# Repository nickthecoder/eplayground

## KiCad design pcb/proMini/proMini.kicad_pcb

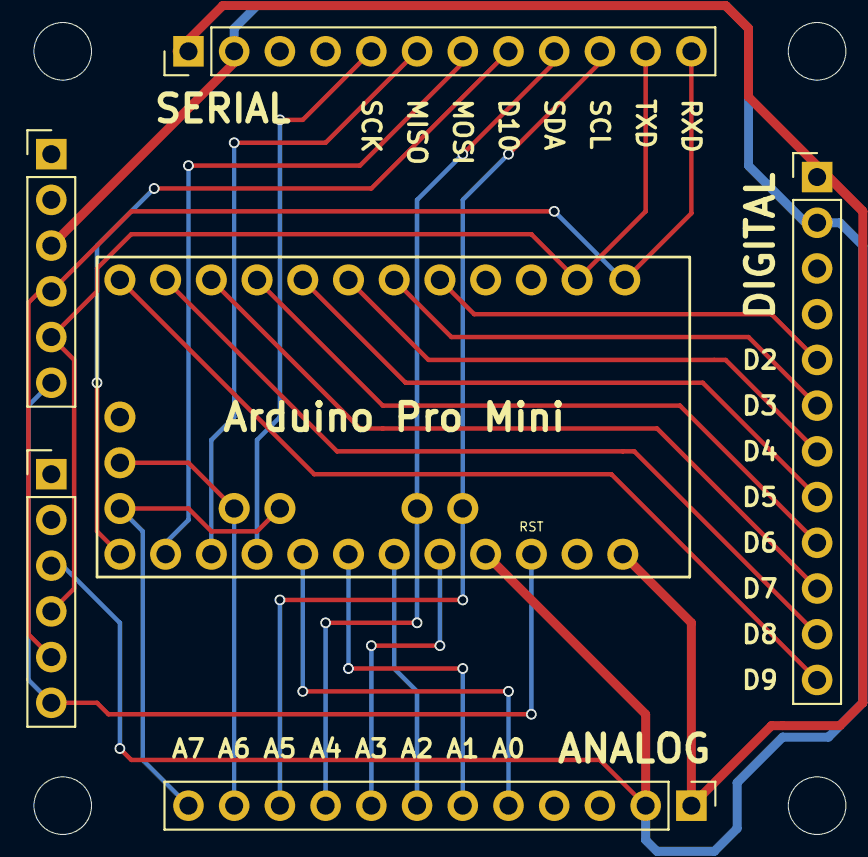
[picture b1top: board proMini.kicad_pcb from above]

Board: 2 copper layers, 8 parts (0 on the bottom side), 26 nets.

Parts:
FT1, FT2: FTDI; Pin_Header_Straight_1x06_Pitch2.54mm
O1: SerialOutput; Socket_Strip_Straight_1x12_Pitch2.54mm
O2, O3: Output; Socket_Strip_Straight_1x12_Pitch2.54mm
X: M3; MountingHole_3.2mm_M3
X#2: M3; MountingHole_3.2mm_M3
XA1: Arduino_Mini_01_Socket; Arduino_ProMini_NoICSP

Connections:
/A0: O3.5, XA1.A0
/A1: O3.6, XA1.A1
/A2: O3.7, XA1.A2
/A3: O3.8, XA1.A3
/A4: O1.9, O3.9, XA1.A4
/A5: O1.10, O3.10, XA1.A5
/A6: O3.11, XA1.A6
/A7: O3.12, XA1.A7
/D0: FT1.5, FT2.4, O1.12, XA1.D0
/D1: FT1.4, FT2.5, O1.11, XA1.D1
/D2: O2.5, XA1.D2
/D3: O2.6, XA1.D3
/D4: O2.7, XA1.D4
/D5: O2.8, XA1.D5
/D6: O2.9, XA1.D6
/D7: O2.10, XA1.D7
/D8: O2.11, XA1.D8
/D9: O2.12, XA1.D9
/D10: O1.8, XA1.D10
/D11: O1.7, XA1.D11
/D12: O1.6, XA1.D12
/D13: O1.5, XA1.D13
/GND: FT1.1, FT1.2, FT2.1, FT2.2, O1.3, O2.3, O3.3, XA1.GND2, XA1.GND4
/RESET: FT1.6, FT2.6, XA1.RST2
/VCC: FT1.3, FT2.3, O1.2, O2.2, O3.2, XA1.5V1
/VIN: O1.1, O2.1, O3.1, XA1.VIN

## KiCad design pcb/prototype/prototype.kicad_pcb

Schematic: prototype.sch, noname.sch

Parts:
H1: Headers8L; Pin_Header_Straight_1x08_Pitch2.54mm
H4: Headers8; Pin_Header_Straight_1x08_Pitch2.54mm
I1, I2: Input; Pin_Header_Straight_1x12_Pitch2.54mm
J1, J2, J3, J4, J5, J6, J7, J8: GS2
J9, J10, J11: Conn_01x14; Pin_Header_Straight_1x14_Pitch2.54mm
J12, J13: Conn_01x08; Pin_Header_Straight_1x08_Pitch2.54mm
O1, O2: Output; Socket_Strip_Straight_1x12_Pitch2.54mm

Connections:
/L0: H1.1 (H1), I1.5 (L0), J1.2 (G2)
/L1: H1.2 (H2), I1.6 (L1), J2.2 (G2)
/L2: H1.3 (H3), I1.7 (L2), J3.2 (G2)
/L3: H1.4 (H4), I1.8 (L3), J4.2 (G2)
/L4: H1.5 (H5), I1.9 (L4), J5.2 (G2)
/L5: H1.6 (H6), I1.10 (L5), J6.2 (G2)
/L6: H1.7 (H7), I1.11 (L6), J7.2 (G2)
/L7: H1.8 (H8), I1.12 (L7), J8.2 (G2)
/VCC: I1.2 (VCC), I2.2 (VCC), J10.1, J10.2, J10.3, J10.4, J10.5, J10.6, J10.7, J10.8, J10.9, J10.10, J10.11, J10.12, J10.13, J10.14, O1.2 (VCC), O2.2 (VCC)
/VIN: I1.1 (VIN), I2.1 (VIN), J11.1, J11.2, J11.3, J11.4, J11.5, J11.6, J11.7, J11.8, J11.9, J11.10, J11.11, J11.12, J11.13, J11.14, O1.1 (VIN), O2.1 (VIN)
Earth: I1.3 (GND), I2.3 (GND), J9.1, J9.2, J9.3, J9.4, J9.5, J9.6, J9.7, J9.8, J9.9, J9.10, J9.11, J9.12, J9.13, J9.14, O1.3 (GND), O2.3 (GND)
unnamed: H4.1 (H1), J1.1 (G1), O2.5 (L0)
unnamed: H4.2 (H2), J2.1 (G1), O2.6 (L1)
unnamed: H4.3 (H3), J3.1 (G1), O2.7 (L2)
unnamed: H4.4 (H4), J4.1 (G1), O2.8 (L3)
unnamed: H4.5 (H5), J5.1 (G1), O2.9 (L4)
unnamed: H4.6 (H6), J6.1 (G1), O2.10 (L5)
unnamed: H4.7 (H7), J7.1 (G1), O2.11 (L6)
unnamed: H4.8 (H8), J8.1 (G1), O2.12 (L7)
unnamed: I2.5 (L0), J13.1
unnamed: I2.6 (L1), J13.2
unnamed: I2.7 (L2), J13.3
unnamed: I2.8 (L3), J13.4
unnamed: I2.9 (L4), J13.5
unnamed: I2.10 (L5), J13.6
unnamed: I2.11 (L6), J13.7
unnamed: I2.12 (L7), J13.8
unnamed: J12.1, O1.12 (L7)
unnamed: J12.2, O1.11 (L6)
unnamed: J12.3, O1.10 (L5)
unnamed: J12.4, O1.9 (L4)
unnamed: J12.5, O1.8 (L3)
unnamed: J12.6, O1.7 (L2)
unnamed: J12.7, O1.6 (L1)
unnamed: J12.8, O1.5 (L0)

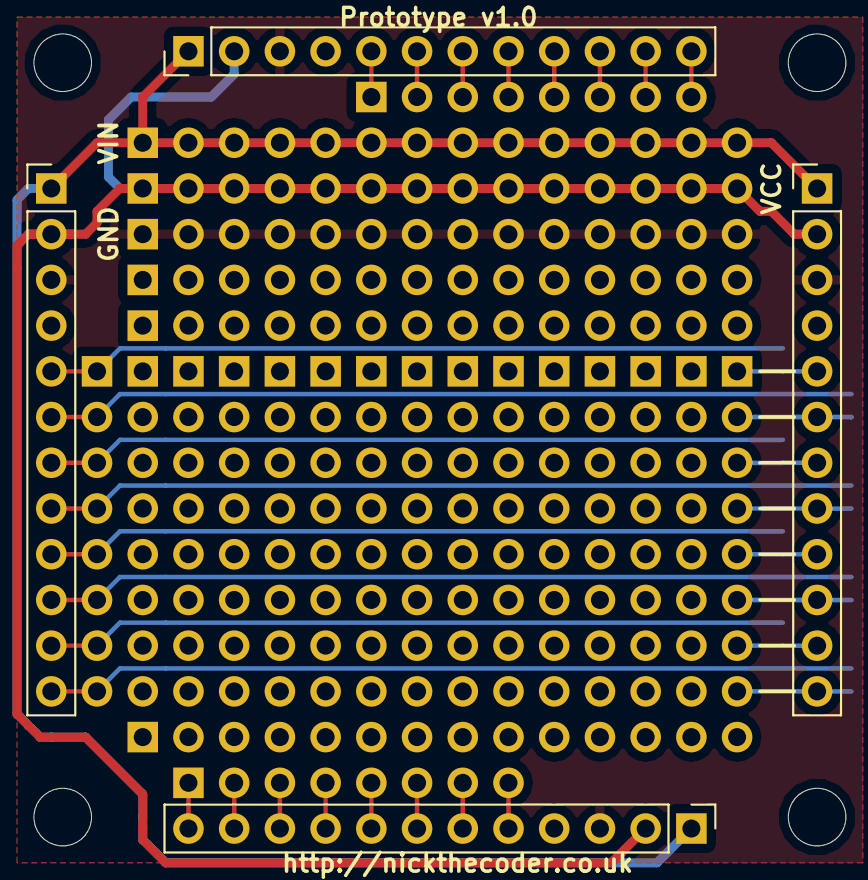
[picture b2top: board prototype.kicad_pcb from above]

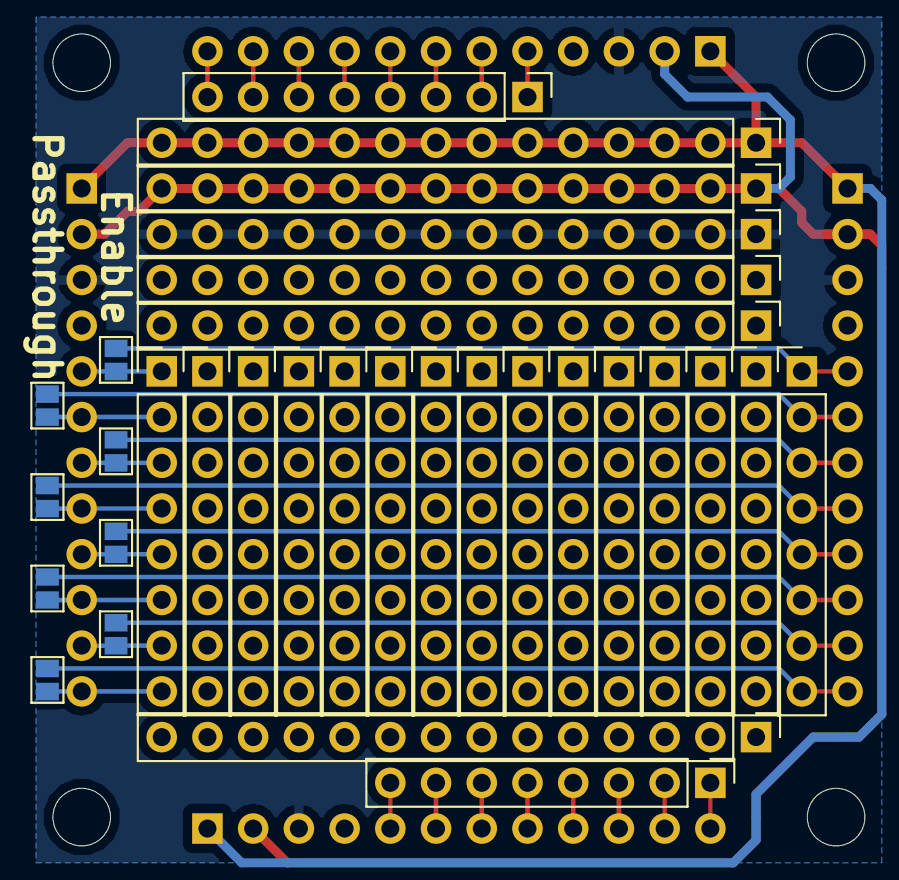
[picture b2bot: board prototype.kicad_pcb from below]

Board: 2 copper layers, 21 parts (15 on the bottom side), 35 nets.

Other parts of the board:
M3, M3#2: MountingHole_3.2mm_M3

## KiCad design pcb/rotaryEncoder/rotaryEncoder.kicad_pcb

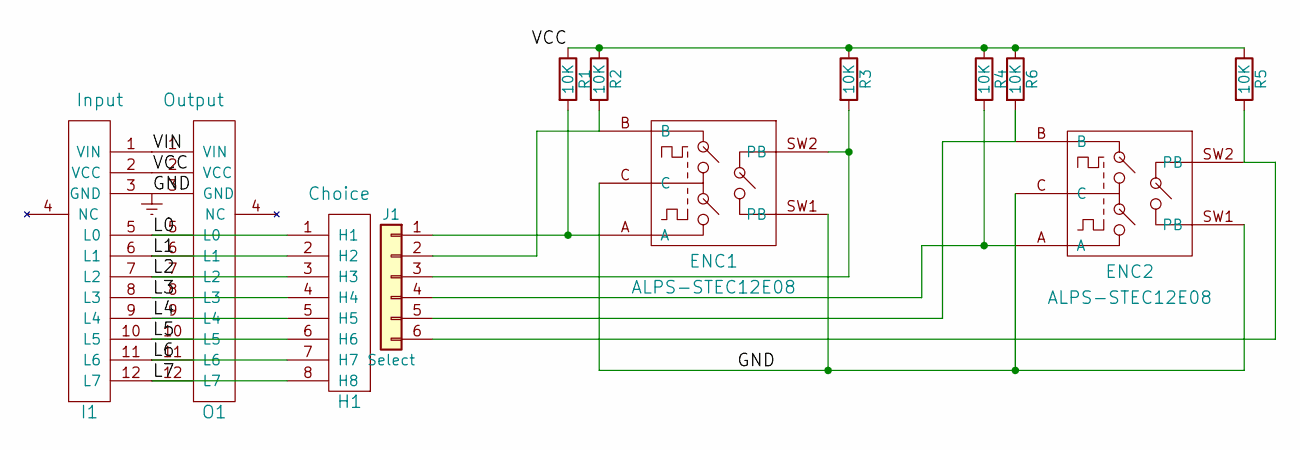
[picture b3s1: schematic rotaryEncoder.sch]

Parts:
ENC1, ENC2: ALPS-STEC12E08; ALPS_STEC12E08
H1: Choice; Pin_Header_Straight_1x08_Pitch2.54mm
I1: Input; Pin_Header_Straight_1x12_Pitch2.54mm
J1: Select; Pin_Header_Straight_1x06_Pitch2.54mm
O1: Output; Socket_Strip_Straight_1x12_Pitch2.54mm
R1, R2, R3, R4, R5, R6: 10K; R_Axial_DIN0204_L3.6mm_D1.6mm_P7.62mm_Horizontal

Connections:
/L0: H1.1 (H1), I1.5 (L0), O1.5 (L0)
/L1: H1.2 (H2), I1.6 (L1), O1.6 (L1)
/L2: H1.3 (H3), I1.7 (L2), O1.7 (L2)
/L3: H1.4 (H4), I1.8 (L3), O1.8 (L3)
/L4: H1.5 (H5), I1.9 (L4), O1.9 (L4)
/L5: H1.6 (H6), I1.10 (L5), O1.10 (L5)
/L6: H1.7 (H7), I1.11 (L6), O1.11 (L6)
/L7: H1.8 (H8), I1.12 (L7), O1.12 (L7)
/VCC: I1.2 (VCC), O1.2 (VCC), R1.1, R2.1, R3.1, R4.1, R5.1, R6.1
/VIN: I1.1 (VIN), O1.1 (VIN)
Earth: ENC1.C, ENC1.SW1 (PB), ENC2.C, ENC2.SW1 (PB), I1.3 (GND), O1.3 (GND)
unnamed: ENC1.A, J1.1, R1.2
unnamed: ENC1.B, J1.2, R2.2
unnamed: ENC1.SW2 (PB), J1.3, R3.2
unnamed: ENC2.A, J1.4, R4.2
unnamed: ENC2.B, J1.5, R6.2
unnamed: ENC2.SW2 (PB), J1.6, R5.2

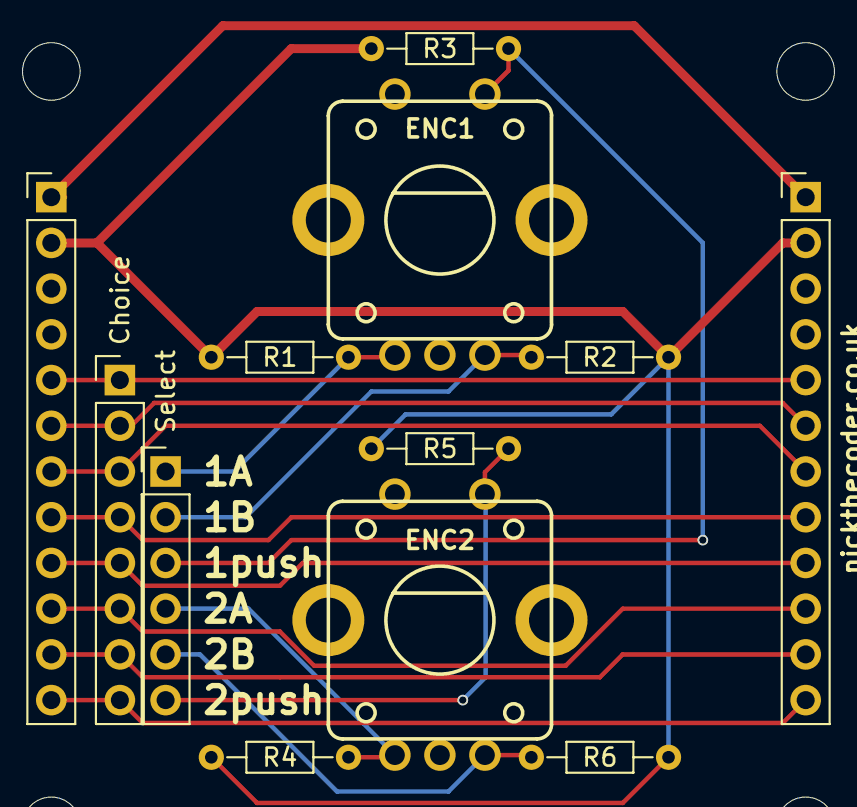
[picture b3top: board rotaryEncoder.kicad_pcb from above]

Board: 2 copper layers, 14 parts (0 on the bottom side), 17 nets.

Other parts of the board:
M3, M3#2: MountingHole_3.2mm_M3

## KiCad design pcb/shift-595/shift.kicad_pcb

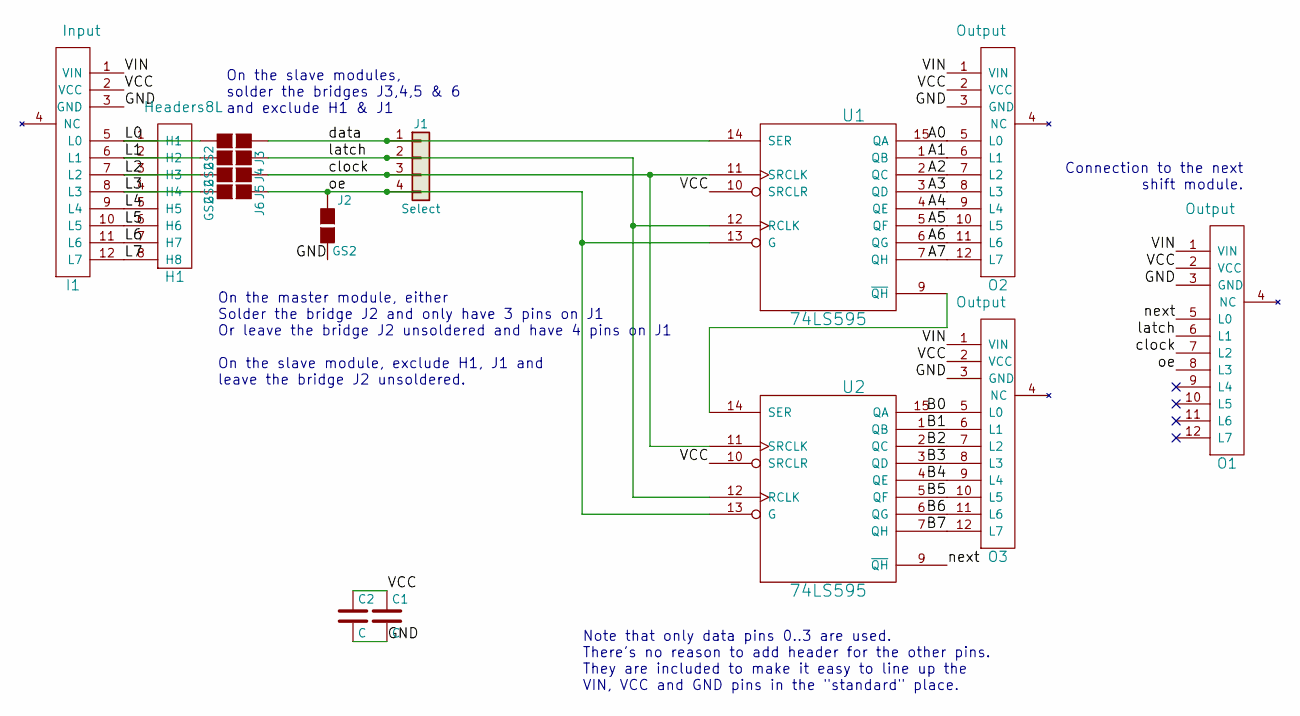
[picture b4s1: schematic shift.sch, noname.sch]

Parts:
C1, C2: C; C_Disc_D3.0mm_W2.0mm_P2.50mm
H1: Headers8L; Pin_Header_Straight_1x08_Pitch2.54mm
I1: Input; Pin_Header_Straight_1x12_Pitch2.54mm
J1: Select; Pin_Header_Straight_1x04_Pitch2.54mm
J2, J3, J4, J5, J6: GS2
O1, O2, O3: Output; Socket_Strip_Straight_1x12_Pitch2.54mm
U1, U2: 74LS595; DIP-16_W7.62mm

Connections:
/A0: O2.5 (L0), U1.15 (QA)
/A1: O2.6 (L1), U1.1 (QB)
/A2: O2.7 (L2), U1.2 (QC)
/A3: O2.8 (L3), U1.3 (QD)
/A4: O2.9 (L4), U1.4 (QE)
/A5: O2.10 (L5), U1.5 (QF)
/A6: O2.11 (L6), U1.6 (QG)
/A7: O2.12 (L7), U1.7 (QH)
/B0: O3.5 (L0), U2.15 (QA)
/B1: O3.6 (L1), U2.1 (QB)
/B2: O3.7 (L2), U2.2 (QC)
/B3: O3.8 (L3), U2.3 (QD)
/B4: O3.9 (L4), U2.4 (QE)
/B5: O3.10 (L5), U2.5 (QF)
/B6: O3.11 (L6), U2.6 (QG)
/B7: O3.12 (L7), U2.7 (QH)
/L0: H1.1 (H1), I1.5 (L0), J3.2 (G2)
/L1: H1.2 (H2), I1.6 (L1), J4.2 (G2)
/L2: H1.3 (H3), I1.7 (L2), J5.2 (G2)
/L3: H1.4 (H4), I1.8 (L3), J6.2 (G2)
/L4: H1.5 (H5), I1.9 (L4)
/L5: H1.6 (H6), I1.10 (L5)
/L6: H1.7 (H7), I1.11 (L6)
/L7: H1.8 (H8), I1.12 (L7)
/VIN: I1.1 (VIN), O1.1 (VIN), O2.1 (VIN), O3.1 (VIN)
/clock: J1.3, J5.1 (G1), O1.7 (L2), U1.11 (SRCLK), U2.11 (SRCLK)
/data: J1.1, J3.1 (G1), U1.14 (SER)
/latch: J1.2, J4.1 (G1), O1.6 (L1), U1.12 (RCLK), U2.12 (RCLK)
/next: O1.5 (L0), U2.9 (~QH)
/oe: J1.4, J2.1 (G1), J6.1 (G1), O1.8 (L3), U1.13 (G), U2.13 (G)
GND: C1.2, C2.2, I1.3 (GND), J2.2 (G2), O1.3 (GND), O2.3 (GND), O3.3 (GND), U1.8 (GND), U2.8 (GND)
unnamed: U1.9 (~QH), U2.14 (SER)
VCC: C1.1, C2.1, I1.2 (VCC), O1.2 (VCC), O2.2 (VCC), O3.2 (VCC), U1.10 (SRCLR), U1.16 (VCC), U2.10 (SRCLR), U2.16 (VCC)

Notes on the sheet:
Connection to the next shift module.
Note that only data pins 0..3 are used. There's no reason to add header for the other pins. They are included to make it easy to line up the VIN, VCC and GND pins in the "standard" place.
On the master module, either Solder the bridge J2 and only have 3 pins on J1 Or leave the bridge J2 unsoldered and have 4 pins on J1 On the slave module, exclude H1, J1 and leave the bridge J2 unsoldered.
On the slave modules, solder the bridges J3,4,5 & 6 and exclude H1 & J1

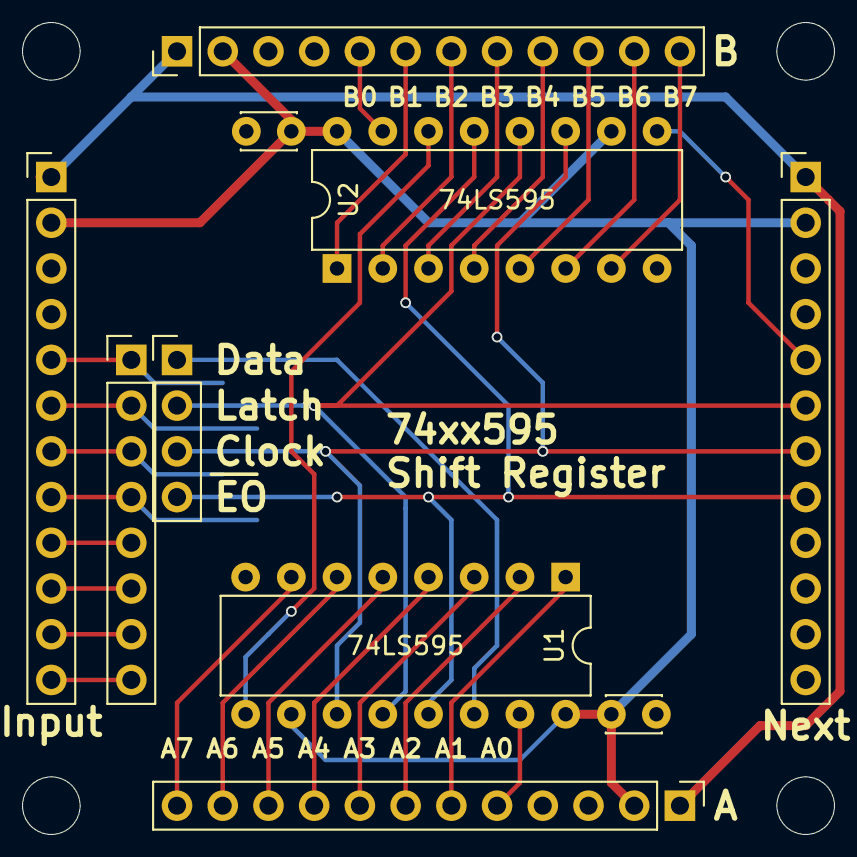
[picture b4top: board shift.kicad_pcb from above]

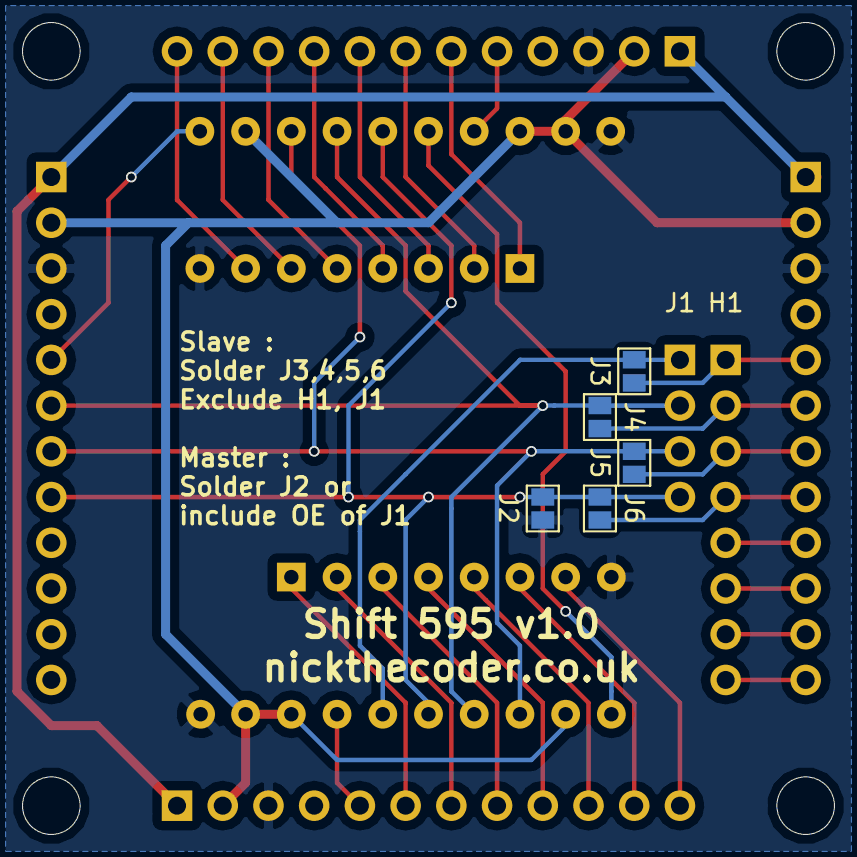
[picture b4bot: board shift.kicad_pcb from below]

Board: 2 copper layers, 17 parts (5 on the bottom side), 33 nets.

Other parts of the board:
M3, M3#2: MountingHole_3.2mm_M3

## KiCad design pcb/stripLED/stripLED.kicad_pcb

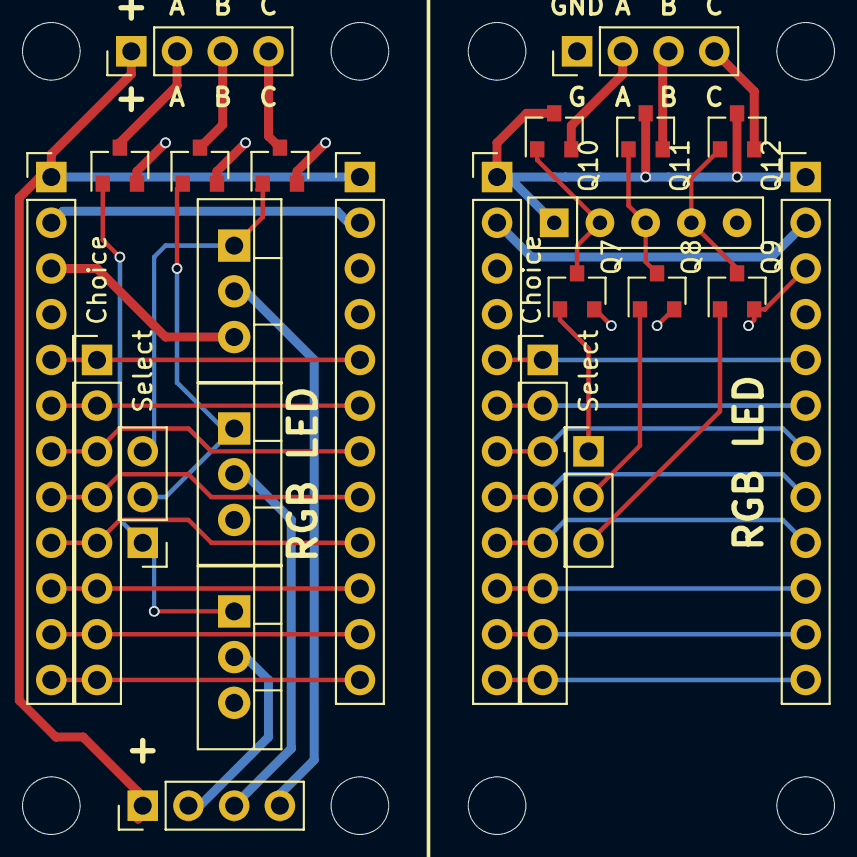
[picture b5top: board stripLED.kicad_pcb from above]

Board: 2 copper layers, 28 parts (0 on the bottom side), 40 nets.

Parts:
H1, H2: Choice; Pin_Header_Straight_1x08_Pitch2.54mm
I1, I2: Input; Pin_Header_Straight_1x12_Pitch2.54mm
J1, J4, J8: Term; Pin_Header_Straight_1x04_Pitch2.54mm
J2, J3: Select; Pin_Header_Straight_1x03_Pitch2.54mm
M3, M3#2: X; MountingHole_3.2mm_M3
O1, O2: Output; Socket_Strip_Straight_1x12_Pitch2.54mm
Q1, Q2, Q3: BSS138; SOT-23
Q4, Q5, Q6: IRLB8721PBF; TO-220_Vertical
Q7, Q8, Q9: BSS83P; SOT-23
Q10, Q11, Q12: 2N7002; SOT-23
RN1: 10K; R_Array_SIP5
X: M3; MountingHole_3.2mm_M3
X#2: M3; MountingHole_3.2mm_M3

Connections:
/D0: H2.1, I2.5, O2.5
/D1: H2.2, I2.6, O2.6
/D2: H2.3, I2.7, O2.7
/D3: H2.4, I2.8, O2.8
/D4: H2.5, I2.9, O2.9
/D5: H2.6, I2.10, O2.10
/D6: H2.7, I2.11, O2.11
/D7: H2.8, I2.12, O2.12
/GND2: I2.3, J4.1, O2.3, Q7.2, Q8.2, Q9.2
/L0: H1.1, I1.5, O1.5
/L1: H1.2, I1.6, O1.6
/L2: H1.3, I1.7, O1.7
/L3: H1.4, I1.8, O1.8
/L4: H1.5, I1.9, O1.9
/L5: H1.6, I1.10, O1.10
/L6: H1.7, I1.11, O1.11
/L7: H1.8, I1.12, O1.12
/VCC: I1.2, O1.2
/VCC2: I2.2, O2.2
/VIN: I1.1, J1.1, J8.1, O1.1
/VIN2: I2.1, O2.1, Q10.3, Q11.3, Q12.3, RN1.1
/gate1: J3.1, Q7.1
/gate2: J3.2, Q8.1
/gate3: J3.3, Q9.1
/gate4: Q7.3, Q10.1, RN1.2
/gate5: Q8.3, Q11.1, RN1.3
/gate6: Q9.3, Q12.1, RN1.4
Earth: I1.3, O1.3, Q1.2, Q2.2, Q3.2, Q4.3, Q5.3, Q6.3
unnamed: J1.2, Q3.3
unnamed: J1.3, Q2.3
unnamed: J1.4, Q1.3
unnamed: J2.1, Q3.1, Q6.1
unnamed: J2.2, Q2.1, Q5.1
unnamed: J2.3, Q1.1, Q4.1
unnamed: J4.2, Q10.2
unnamed: J4.3, Q11.2
unnamed: J4.4, Q12.2
unnamed: J8.2, Q6.2
unnamed: J8.3, Q5.2
unnamed: J8.4, Q4.2

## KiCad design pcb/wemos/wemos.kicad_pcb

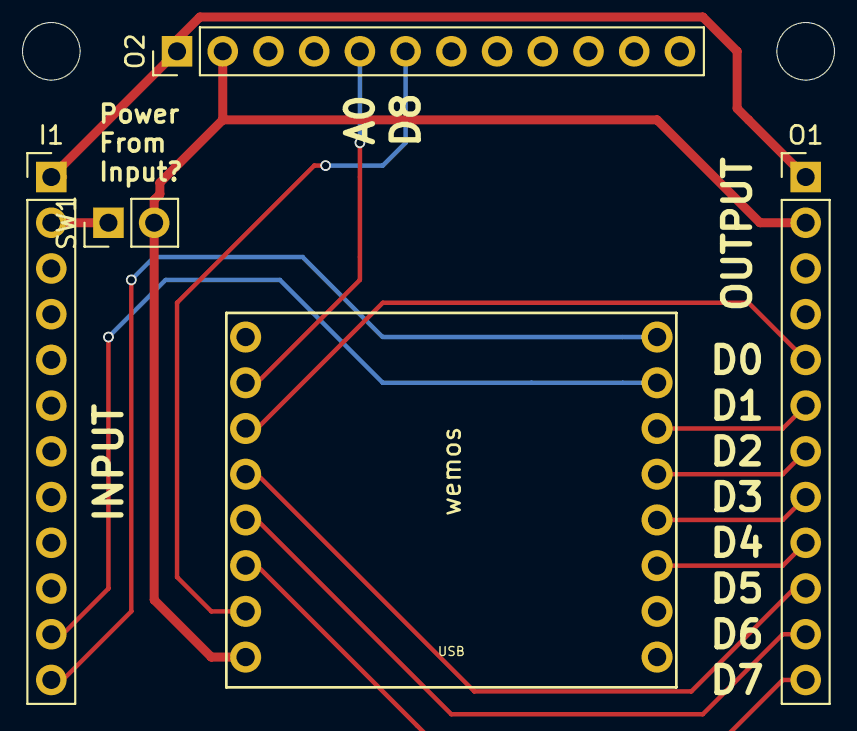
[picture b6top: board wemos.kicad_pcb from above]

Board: 2 copper layers, 7 parts (0 on the bottom side), 16 nets.

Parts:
I1: SerialInput; Socket_Strip_Straight_1x12_Pitch2.54mm
M3, M3#2: MountingHole_3.2mm_M3
O1, O2: Output; Socket_Strip_Straight_1x12_Pitch2.54mm
SW1: SW_SPST; Pin_Header_Straight_1x02_Pitch2.54mm
U1: wemos

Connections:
/A0: O2.5, U1.10
/D0: O1.5, U1.11
/D1: O1.6, U1.6
/D2: O1.7, U1.5
/D3: O1.8, U1.4
/D4: O1.9, U1.3
/D5: O1.10, U1.12
/D6: O1.11, U1.13
/D7: O1.12, U1.14
/D8: O2.6, U1.15
/RX: I1.11, U1.7
/TX: I1.12, U1.8
/VCC: O1.2, O2.2, SW1.2, U1.16
/VIN: I1.1, O1.1, O2.1
Earth: I1.3, O1.3, O2.3, U1.2
unnamed: I1.2, SW1.1
